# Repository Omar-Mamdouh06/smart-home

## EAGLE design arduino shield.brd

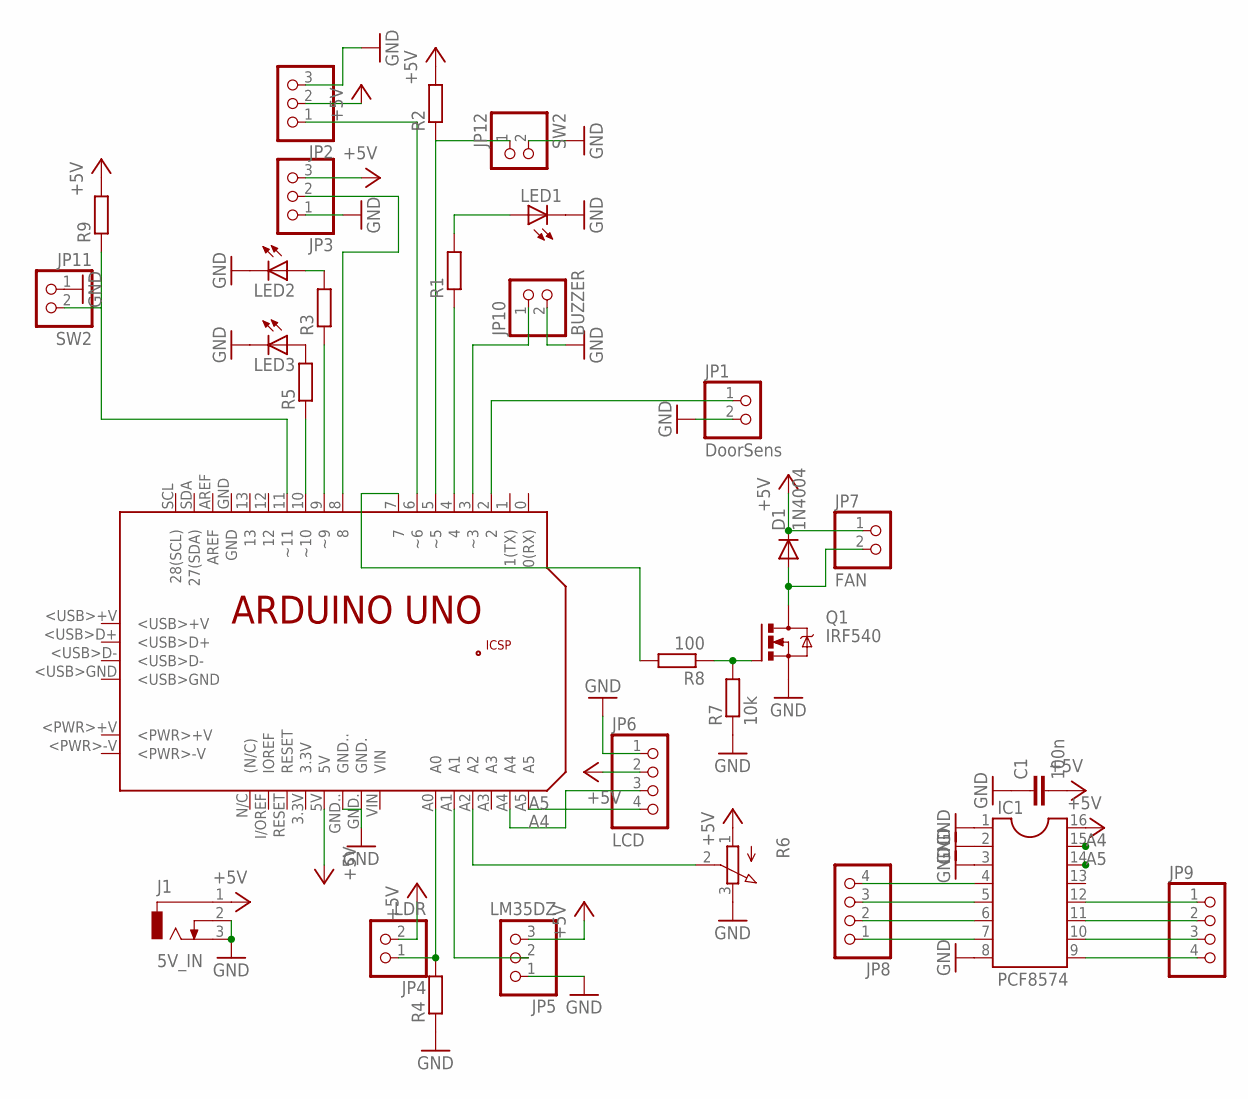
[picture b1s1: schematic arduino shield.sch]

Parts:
C1: 100n; C050-024X044
D1: 1N4004; DO41-10
IC1: PCF8574; DIL16
J1: 5V_IN; DCJ0303
JP1: DoorSens; 1X02
JP2, JP3: PINHD-1X3; 1X03
JP4: LDR; 1X02
JP5: LM35DZ; 1X03
JP6: LCD; 1X04
JP7: FAN; 1X02
JP8, JP9: PINHD-1X4; 1X04
JP10: BUZZER; 1X02
JP11, JP12: SW2; 1X02
LED1, LED2, LED3: LED5MM
PCB1: ARDUINO_UNO
Q1: IRF540; TO220BV
R1, R2, R3, R4, R5, R9: R-EU_0207/7; 0207/7
R6: 3RP/1610N
R7: 10k; 0207/7
R8: 100; 0207/7

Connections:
+5V: C1.2, D1.C, IC1.16, J1.1, JP2.2, JP3.3, JP4.2, JP5.3, JP6.2, JP7.1, PCB1.5V, R2.2, R6.1 (A), R9.2
A4: IC1.15, JP6.3, PCB1.A4
A5: IC1.14, JP6.4, PCB1.A5
GND: C1.1, IC1.1, IC1.2, IC1.3, IC1.8, J1.2, J1.3, JP1.2, JP2.3, JP3.1, JP5.1, JP6.1, JP10.2, JP11.1, JP12.2, LED1.K (C), LED2.K (C), LED3.K (C), PCB1.GND., PCB1.GND.., Q1.S, R4.1, R6.3 (E), R7.1
unnamed: JP10.1, PCB1.3 (~3)
unnamed: LED1.A, R1.2
unnamed: PCB1.4, R1.1
unnamed: JP1.1, PCB1.2
unnamed: JP12.1, PCB1.5 (~5), R2.1
unnamed: JP2.1, PCB1.6 (~6)
unnamed: JP3.2, PCB1.8
unnamed: LED2.A, R3.2
unnamed: PCB1.9 (~9), R3.1
unnamed: JP4.1, PCB1.A0, R4.2
unnamed: JP11.2, PCB1.11 (~11), R9.1
unnamed: LED3.A, R5.2
unnamed: PCB1.10 (~10), R5.1
unnamed: PCB1.A2, R6.2 (S)
unnamed: JP5.2, PCB1.A1
unnamed: D1.A, JP7.2, Q1.D
unnamed: PCB1.7, R8.2
unnamed: Q1.G, R7.2, R8.1
unnamed: IC1.4, JP8.4
unnamed: IC1.5, JP8.3
unnamed: IC1.6, JP8.2
unnamed: IC1.7, JP8.1
unnamed: IC1.9, JP9.4
unnamed: IC1.10, JP9.3
unnamed: IC1.11, JP9.2
unnamed: IC1.12, JP9.1

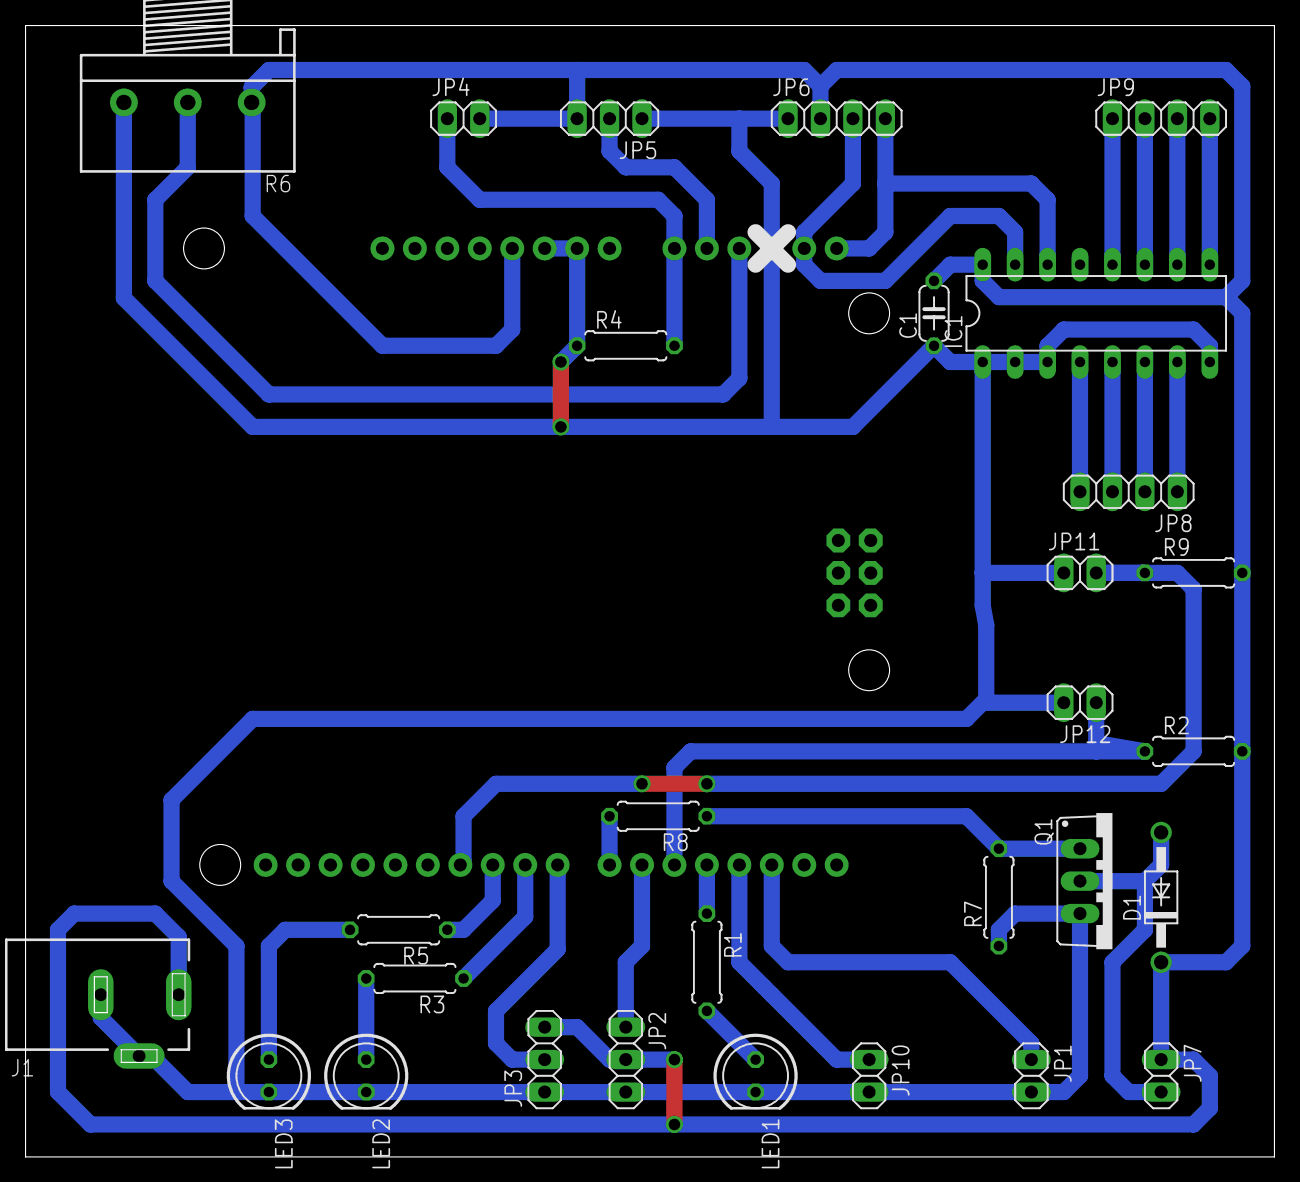
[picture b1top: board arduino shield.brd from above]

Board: 2 copper layers, 97.8 x 88.6 mm, 30 parts (1 on the bottom side), 30 nets.
